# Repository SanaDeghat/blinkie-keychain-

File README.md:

sooo this is a ablinkeie (keychain) that looks like a bow tie(very cute if u ask me). Ngl I have no clue where one would use this, or why would one wnat this but ig its nice for giving someone a seizure. uhhhh beside taht i used kicad to make it, I made an account on this really schechy website to download one of the footprints.yeah anyways heres the linkto the lapse of me making this: https://lapse.hackclub.com/timelapse/QtYV9dRXhwVN

Pic for schematic:

pic from PCB

(back is very pretty)

(ALSO IM MAKING THIS TO BUY MYSELF SOME CUTE JELLYCATS HEHE )
Anyways thx for lookign at my project ily whoevers revwing this (ill finish reviewing all the otehr projects )

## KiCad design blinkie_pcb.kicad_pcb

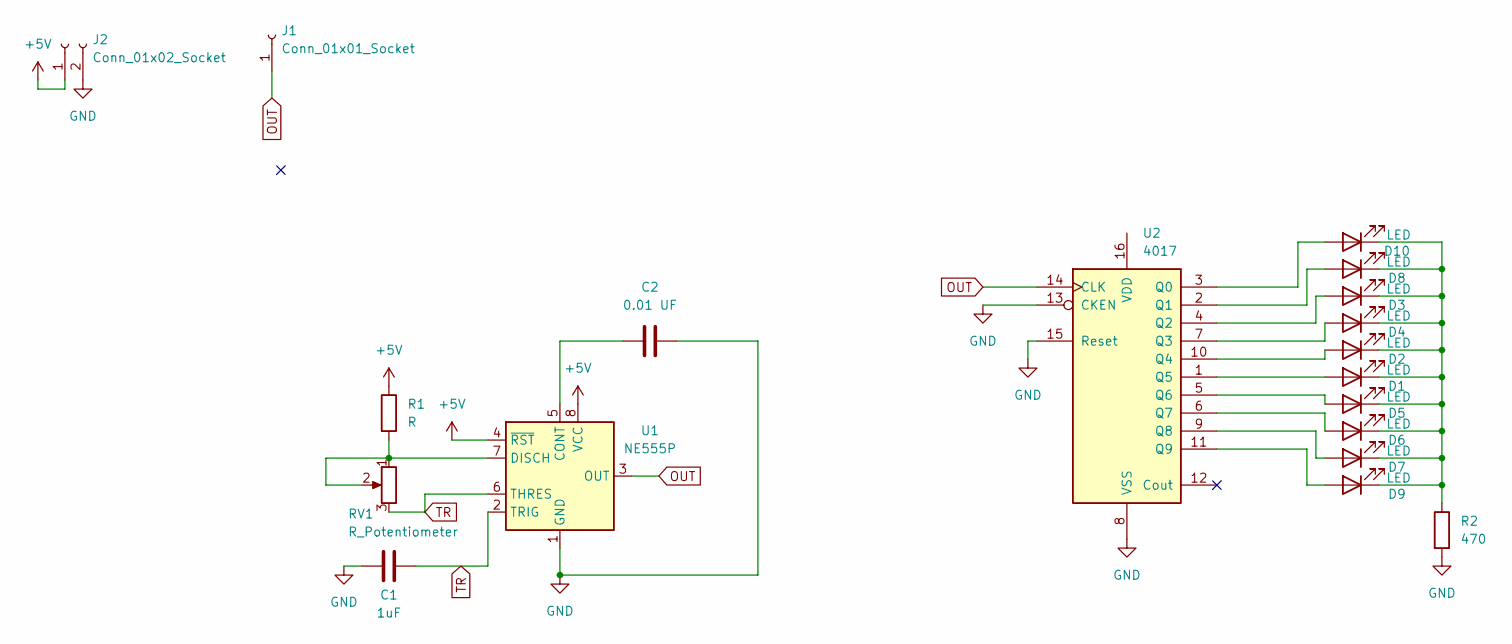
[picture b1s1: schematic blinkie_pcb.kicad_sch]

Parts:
C1: 1uF; CP_Radial_D5.0mm_P2.00mm
C2: 0.01 UF; C_Disc_D7.5mm_W2.5mm_P5.00mm
D1, D2, D3, D4, D5, D6, D7, D8, D9, D10: LED; LED_D3.0mm
J1: Conn_01x01_Socket; PinHeader_1x01_P2.54mm_Vertical
J2: Conn_01x02_Socket; PinHeader_1x02_P2.54mm_Vertical
R1: R; R_Axial_DIN0207_L6.3mm_D2.5mm_P7.62mm_Horizontal
R2: 470; R_Axial_DIN0207_L6.3mm_D2.5mm_P7.62mm_Horizontal
RV1: R_Potentiometer; Potentiometer_Vishay_T93YA_Vertical
U1: NE555P; DIP-8_W7.62mm
U2: 4017; CD4017BE

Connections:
+5V: J2.1, R1.1, U1.4 (~RST), U1.8 (VCC)
GND: C1.1, C2.2, J2.2, R2.2, U1.1 (GND), U2.8 (VSS), U2.13 (CKEN), U2.15 (Reset)
unnamed: D1.2 (A), U2.1 (Q5)
unnamed: D1.1 (K), D2.1 (K), D3.1 (K), D4.1 (K), D5.1 (K), D6.1 (K), D7.1 (K), D8.1 (K), D9.1 (K), D10.1 (K), R2.1
unnamed: D2.2 (A), U2.10 (Q4)
unnamed: D3.2 (A), U2.4 (Q2)
unnamed: D4.2 (A), U2.7 (Q3)
unnamed: D5.2 (A), U2.5 (Q6)
unnamed: D6.2 (A), U2.6 (Q7)
unnamed: D7.2 (A), U2.9 (Q8)
unnamed: D8.2 (A), U2.2 (Q1)
unnamed: D9.2 (A), U2.11 (Q9)
unnamed: D10.2 (A), U2.3 (Q0)
unnamed: C2.1, U1.5 (CONT)
unnamed: R1.2, RV1.1, RV1.2, U1.7 (DISCH)
OUT: J1.1, U1.3 (OUT), U2.14 (CLK)
TR: C1.2, RV1.3, U1.2 (TRIG), U1.6 (THRES)

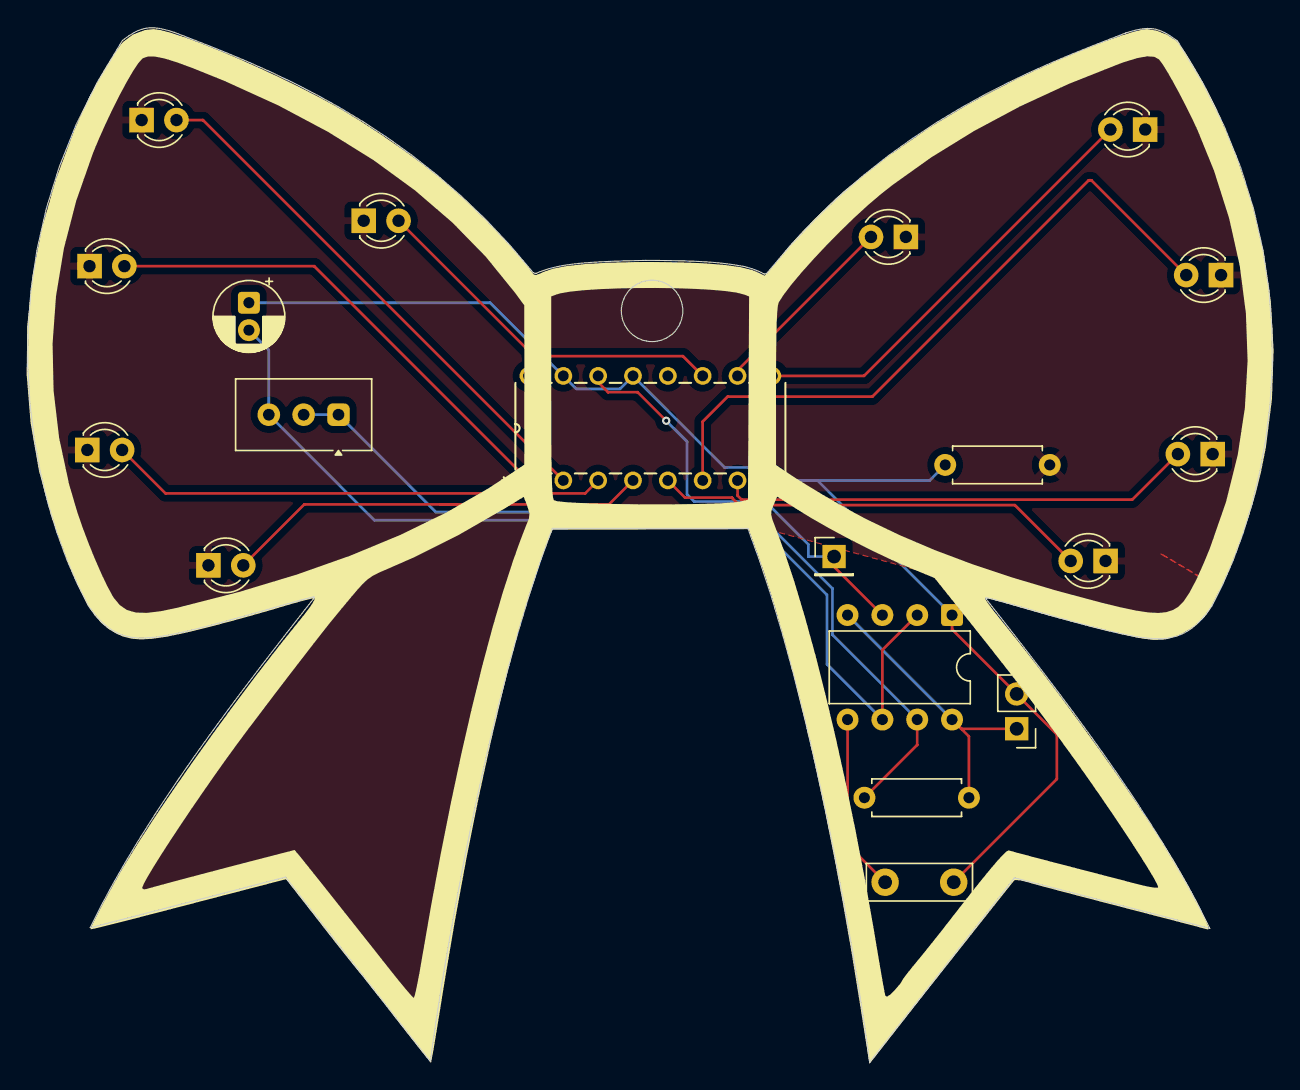
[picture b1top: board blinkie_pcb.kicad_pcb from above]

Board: 2 copper layers, 90.7 x 75.4 mm, 19 parts (0 on the bottom side), 17 nets.

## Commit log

2026-04-05 making the folders of PCBs and hackatime
2026-04-05 finished schematic
2026-04-05 DONEDONEDONEONDOIENE FINALLYYYY MY BACK HURTS
2026-04-05 wrote readme
2026-04-05 so like added evry thing to the read me (pics and all)

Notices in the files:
parts and their libraries:
Copyright 2016 Accelerated Designs. All rights reserved.
